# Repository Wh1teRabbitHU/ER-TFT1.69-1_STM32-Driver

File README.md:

# ER-TFT1.69-1_STM32-Driver

STM32 Driver and Adapter design for the following module:

[LCD Display Panel](https://www.buydisplay.com/1-69-inch-color-280x240-round-rectangle-ips-tft-lcd-display-panel-st7789)

The driver is based on the example code, refactored to work with the Adapter. It can be used standalone or with the adapter board. For standalone usage, you can copy the following files into your own project:

- [```Driver/Core/Inc/ST7789V.h```](Driver/Core/Inc/ST7789V.h)
- [```Driver/Core/Src/ST7789V.c```](Driver/Core/Src/ST7789V.c)
- [```Driver/Core/Inc/font_6_12.h```](Driver/Core/Inc/font_6_12.h)

If you recreate the adapter, then you just need to load the Driver into STM32CubeIDE and program the MCU. The adapter is using a STM32G030C8TX MCU, but you can replace it with any other STM32 if you want to extend the adapter. The only requirement is that you follow the pinout and connect them the same way as in the original design.

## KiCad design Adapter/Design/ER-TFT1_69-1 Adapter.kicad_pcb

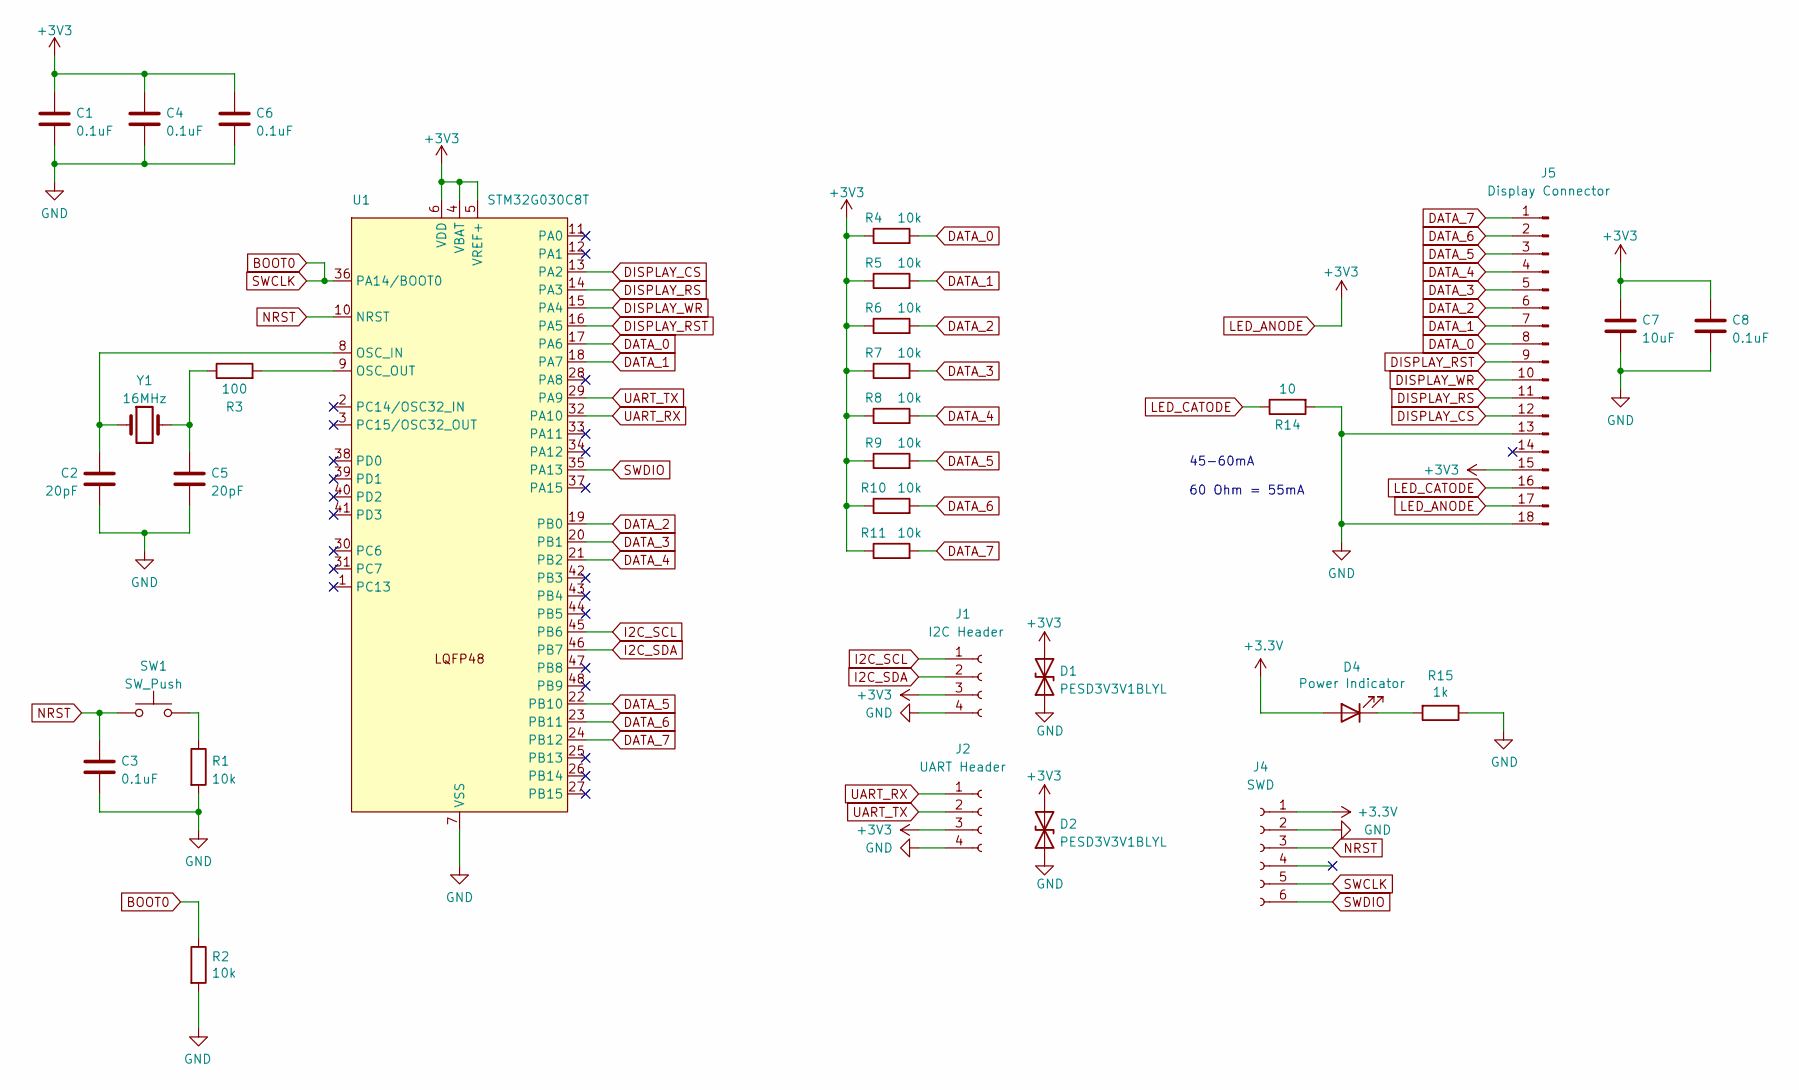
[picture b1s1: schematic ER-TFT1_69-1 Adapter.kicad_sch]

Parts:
C1, C3, C4, C6, C8: 0.1uF; C_0402_1005Metric
C2, C5: 20pF; C_0402_1005Metric
C7: 10uF; C_0805_2012Metric
D1, D2: PESD3V3V1BLYL; SOD882
D4: Power Indicator; LED_0603_1608Metric_Pad1.05x0.95mm_HandSolder
J1: I2C Header; JST_XH_B4B-XH-A_1x04_P2.50mm_Vertical
J2: UART Header; JST_XH_B4B-XH-A_1x04_P2.50mm_Vertical
J4: SWD; AFA07-S06FCA-00
J5: Display Connector; ER-TFT1_69-1_SMD_18PIN
R1, R2, R4, R5, R6, R7, R8, R9, R10, R11: 10k; R_0402_1005Metric
R3: 100; R_0402_1005Metric
R14: 10; C_1206_3216Metric
R15: 1k; R_0402_1005Metric
SW1: SW_Push; SW_SPST_TL3342
U1: STM32G030C8T; LQFP-48_7x7mm_P0.5mm
Y1: 16MHz; Crystal_SMD_HC49-SD

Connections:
BOOT0: J4.5, R2.1, U1.36 (PA14/BOOT0)
DATA_0: J5.8, R4.2, U1.17 (PA6)
DATA_1: J5.7, R5.2, U1.18 (PA7)
DATA_2: J5.6, R6.2, U1.19 (PB0)
DATA_3: J5.5, R7.2, U1.20 (PB1)
DATA_4: J5.4, R8.2, U1.21 (PB2)
DATA_5: J5.3, R9.2, U1.22 (PB10)
DATA_6: J5.2, R10.2, U1.23 (PB11)
DATA_7: J5.1, R11.2, U1.24 (PB12)
DISPLAY_CS: J5.12, U1.13 (PA2)
DISPLAY_RS: J5.11, U1.14 (PA3)
DISPLAY_RST: J5.9, U1.16 (PA5)
DISPLAY_WR: J5.10, U1.15 (PA4)
GND: C1.2, C2.1, C3.2, C4.2, C5.2, C6.2, C7.2, C8.2, D1.1 (A1), D2.1 (A1), J1.4, J2.4, J4.2, J5.13, J5.18, R1.2, R2.2, R14.2, R15.1, U1.7 (VSS)
I2C_SCL: J1.1, U1.45 (PB6)
I2C_SDA: J1.2, U1.46 (PB7)
LED_CATODE: J5.16, R14.1
NRST: C3.1, J4.3, SW1.1, U1.10 (NRST)
unnamed: C2.2, U1.8 (OSC_IN), Y1.1
unnamed: C5.1, R3.1, Y1.2
unnamed: D4.1 (K), R15.2
unnamed: R1.1, SW1.2
unnamed: R3.2, U1.9 (OSC_OUT)
SWDIO: J4.6, U1.35 (PA13)
UART_RX: J2.1, U1.32 (PA10)
UART_TX: J2.2, U1.29 (PA9)

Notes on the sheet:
45-60mA 60 Ohm = 55mA

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
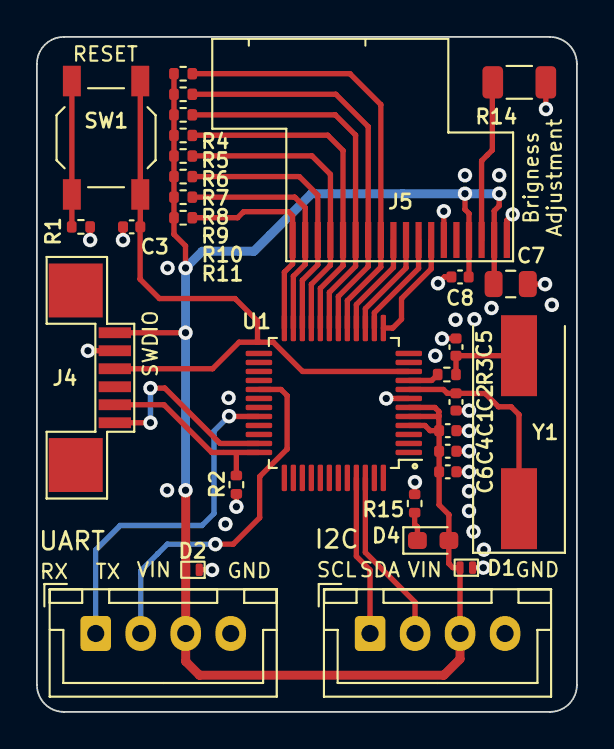
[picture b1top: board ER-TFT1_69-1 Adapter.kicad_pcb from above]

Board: 4 copper layers, 30.0 x 37.5 mm, 31 parts (0 on the bottom side), 27 nets.

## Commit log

2022-09-17 Add design (Rev 2)
2022-09-17 Add assembly and gerber files
2022-09-17 Adding some readme text and images
2022-09-17 Initial Driver implementation
2022-09-17 Updating README
2022-09-18 Refactoring the provided driver and splitting font information into separate file
2022-09-18 Fixing README link
2022-09-18 Small refactors and adding comments
2022-09-18 Color helper
2022-12-21 Adding Kicad files (symbol, footprint and 3D) for the display
